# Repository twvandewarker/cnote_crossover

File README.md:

# cnote_crossover

This is a crossover board for Parts Express's C-Note bookshelf speaker kit: https://www.parts-express.com/c-note-mt-bookshelf-speaker-kit-pair-with-knock-down-cabinets--300-7140

If you want to check out the EAGLE files, you will probably need my parts library, located here: https://github.com/twvandewarker/eagle_library

The zip folder contains the Gerbers that I sent to get my boards. I used JLCPCB.

This board uses the stock crossover components that come with the kit, plus a 6 pin Phoenix-type connector. The one I used is Wurth Electronics 691241610006 and will fit up to 14AWG wire, but any type of connector with 0.4" pitch will work. The mounting holes are 3.5" square, and you can use up to #8 screws. There are holes milled for 1/8" zip ties for the inductors.

There is a place for the optional .22uF cap in parallel with the woofer's inductor. I used Dayton DMPC-0.22. This was suggested by the speaker's designer in the forums to attenuate the woofer around it's cone breakup.

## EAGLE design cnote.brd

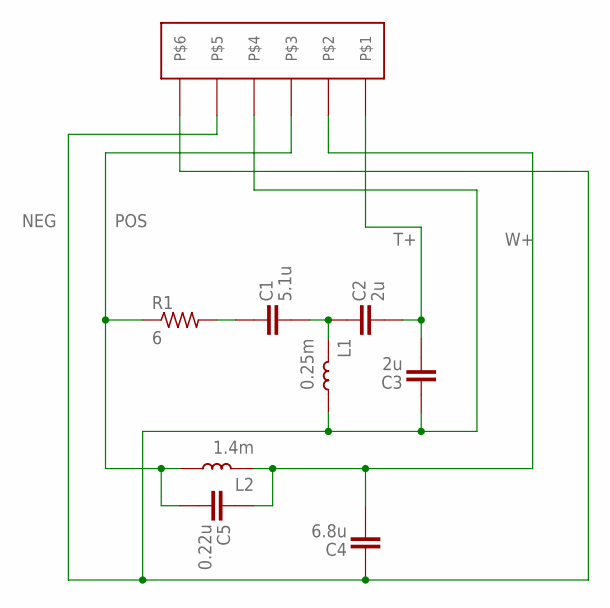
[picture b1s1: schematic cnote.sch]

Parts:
C1: 5.1u; DAYTON_21X31
C2, C3: 2u; DAYTON_13X31
C4: 6.8u; DAYTON_18X45
C5: 0.22u; DAYTON_7X18
L1: 0.25m; DAYTON_AC20-25
L2: 1.4m; DAYTON_AC201-4
R1: 6; DAYTON_48X10
U$1: WURTH_WR-TBL-2416-6

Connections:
unnamed: C1.P$2 (2), C2.P$1 (1), L1.P$2 (2)
unnamed: C1.P$1 (1), R1.P$2 (2)
NEG: C3.P$1 (1), C4.P$1 (1), L1.P$1 (1), U$1.P$4, U$1.P$5, U$1.P$6
POS: C5.P$2 (2), L2.P$1 (1), R1.P$1 (1), U$1.P$3
T+: C2.P$2 (2), C3.P$2 (2), U$1.P$1
W+: C4.P$2 (2), C5.P$1 (1), L2.P$2 (2), U$1.P$2

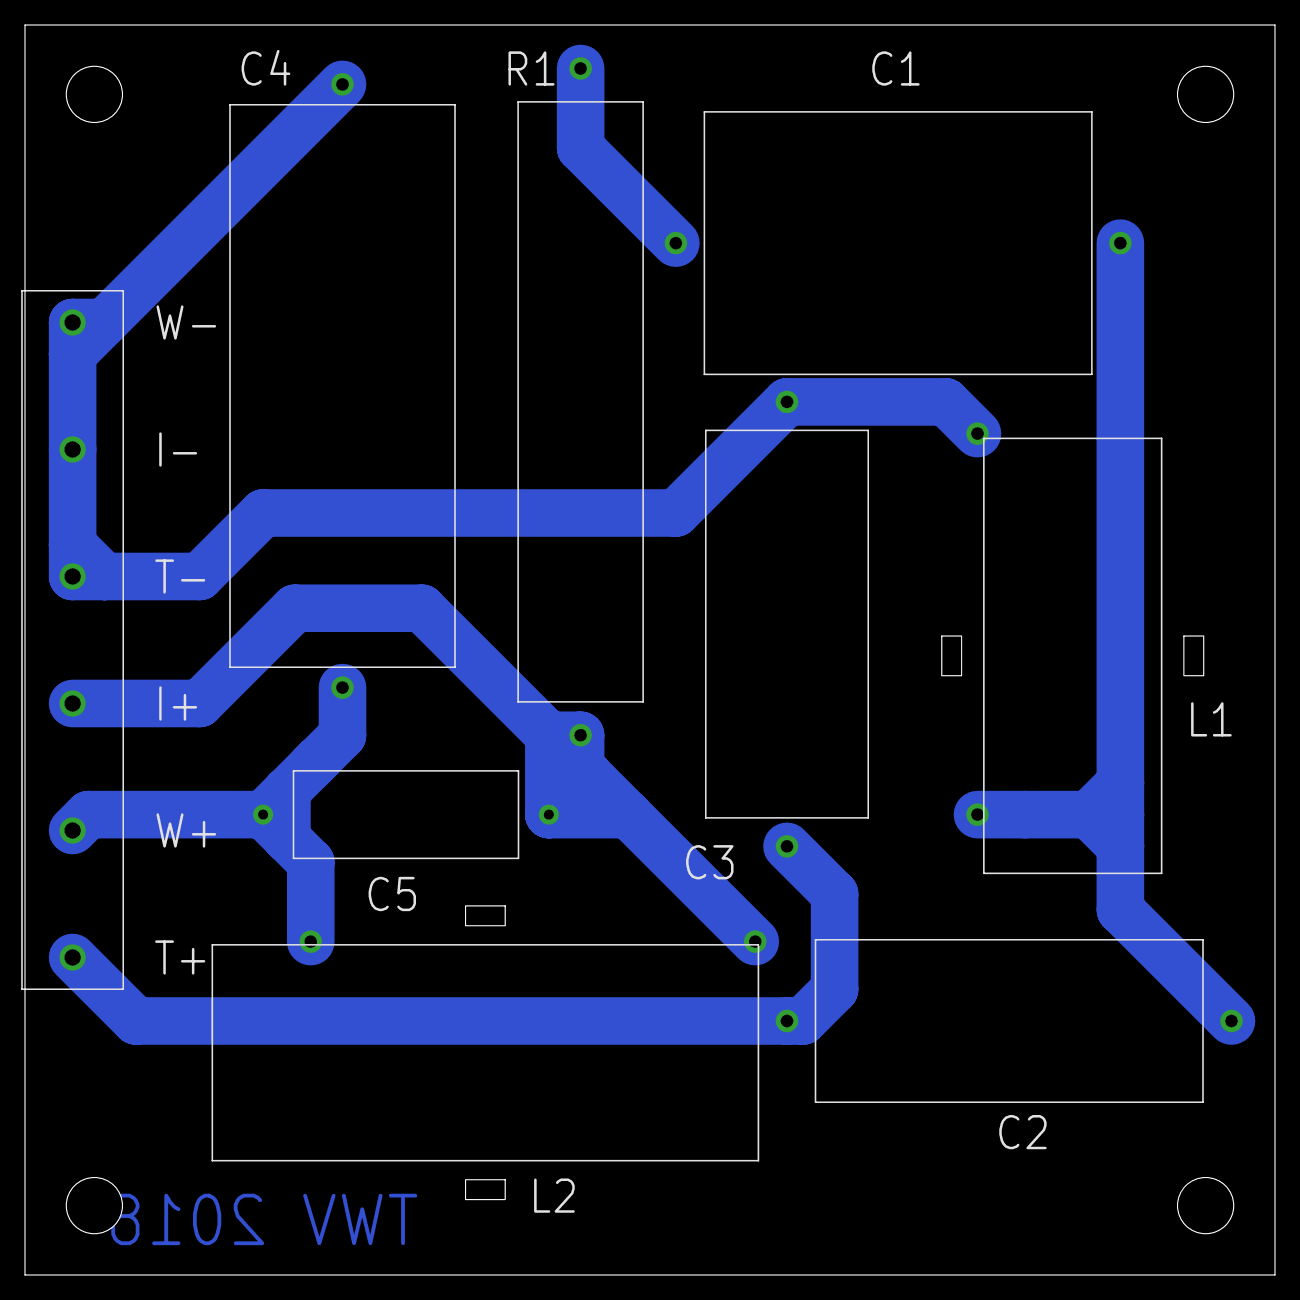
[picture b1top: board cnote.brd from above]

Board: 2 copper layers, 100.0 x 100.0 mm, 9 parts (0 on the bottom side), 6 nets.

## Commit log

2018-12-26 Added files
2018-12-26 Fixed connector part number
2018-12-26 Fixed readme
2018-12-26 Added pdfs
